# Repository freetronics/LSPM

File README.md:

Freetronics LibreSat Prototyping Module
=======================================
Copyright 2012 Freetronics Pty Ltd   www.freetronics.com  

A minimalist general-purpose prototyping module for CubeSat satellites.
Originally designed for ArduSat (www.ardusat.org) but also useful
for other satellite projects and non-space applications.

More information is available at:

  http://www.freetronics.com/lspm

The "docs" folder within this repository includes a handy copy of the
schematic in PDF format and image(s) of the pcb.

INSTALLATION
------------
The design is saved as an EAGLE project. EAGLE PCB design software is
available from www.cadsoftusa.com free for non-commercial use. To use
this project download it and place the directory containing these files
into the "eagle" directory on your computer. Then open EAGLE and
navigate to the project.

DISTRIBUTION
------------
The specific terms of distribution of this project are governed by the
license referenced below.

LICENSE
-------
Licensed under the TAPR Open Hardware License (www.tapr.org/OHL).
The "license" folder within this repository also contains a copy of
this license in plain text format.

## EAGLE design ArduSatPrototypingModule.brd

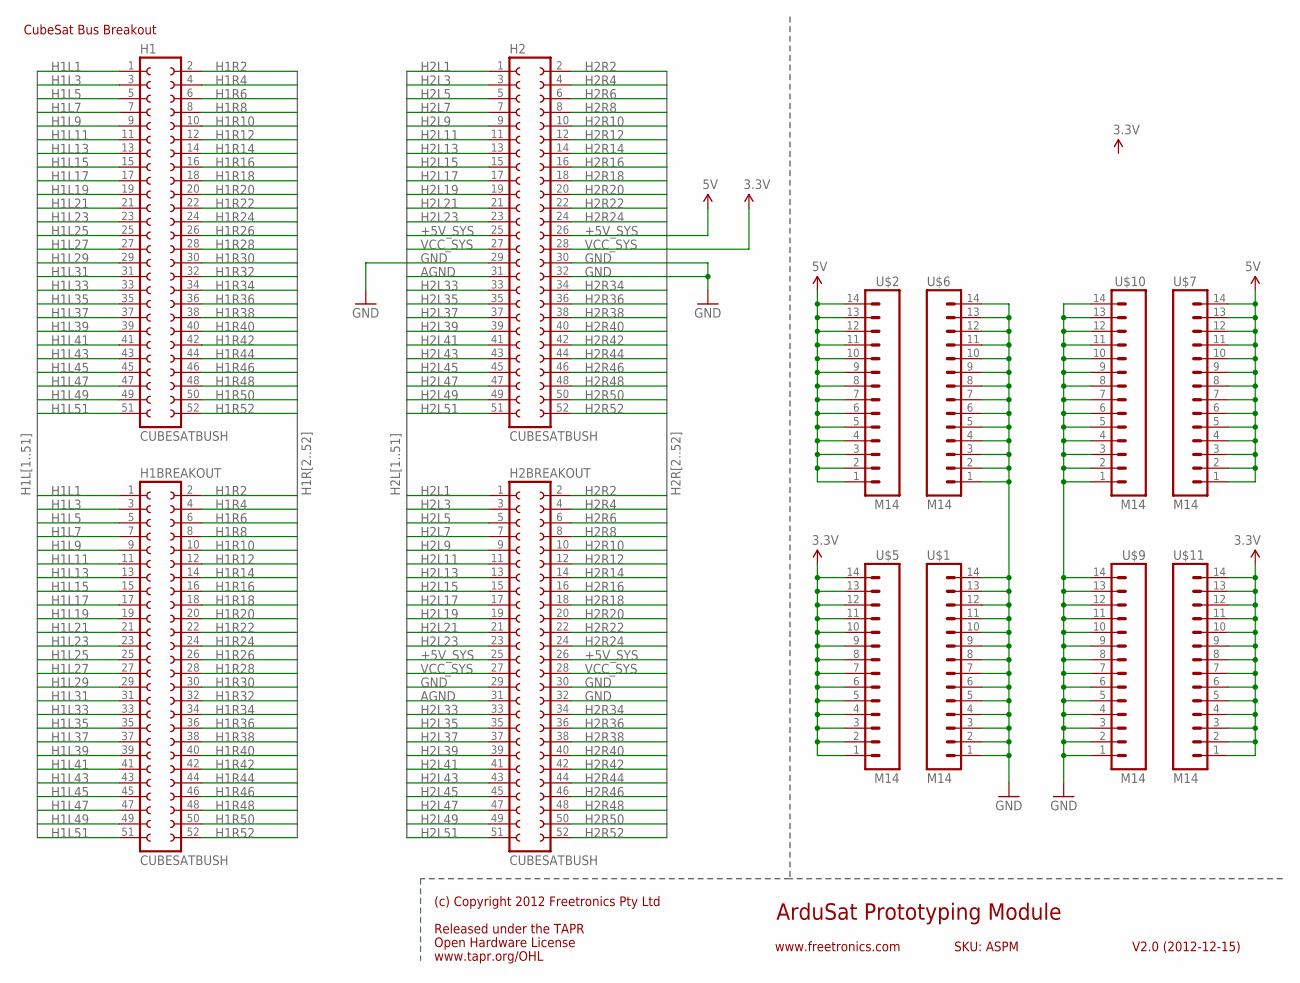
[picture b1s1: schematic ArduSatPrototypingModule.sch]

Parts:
H1, H1BREAKOUT, H2, H2BREAKOUT: CUBESATBUSH; CUBESATBUS
U$1, U$2, U$5, U$6, U$7, U$9, U$10, U$11: M14; 1X14

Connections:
+5V_SYS: H2.25, H2.26, H2BREAKOUT.25, H2BREAKOUT.26, U$2.1, U$2.2, U$2.3, U$2.4, U$2.5, U$2.6, U$2.7, U$2.8, U$2.9, U$2.10, U$2.11, U$2.12, U$2.13, U$2.14, U$7.1, U$7.2, U$7.3, U$7.4, U$7.5, U$7.6, U$7.7, U$7.8, U$7.9, U$7.10, U$7.11, U$7.12, U$7.13, U$7.14
AGND: H2.31, H2BREAKOUT.31
GND: H2.29, H2.30, H2.32, H2BREAKOUT.29, H2BREAKOUT.30, H2BREAKOUT.32, U$1.1, U$1.2, U$1.3, U$1.4, U$1.5, U$1.6, U$1.7, U$1.8, U$1.9, U$1.10, U$1.11, U$1.12, U$1.13, U$1.14, U$6.1, U$6.2, U$6.3, U$6.4, U$6.5, U$6.6, U$6.7, U$6.8, U$6.9, U$6.10, U$6.11, U$6.12, U$6.13, U$6.14, U$9.1, U$9.2, U$9.3, U$9.4, U$9.5, U$9.6, U$9.7, U$9.8, U$9.9, U$9.10, U$9.11, U$9.12, U$9.13, U$9.14, U$10.1, U$10.2, U$10.3, U$10.4, U$10.5, U$10.6, U$10.7, U$10.8, U$10.9, U$10.10, U$10.11, U$10.12, U$10.13, U$10.14
H1L1: H1.1, H1BREAKOUT.1
H1L3: H1.3, H1BREAKOUT.3
H1L5: H1.5, H1BREAKOUT.5
H1L7: H1.7, H1BREAKOUT.7
H1L9: H1.9, H1BREAKOUT.9
H1L11: H1.11, H1BREAKOUT.11
H1L13: H1.13, H1BREAKOUT.13
H1L15: H1.15, H1BREAKOUT.15
H1L17: H1.17, H1BREAKOUT.17
H1L19: H1.19, H1BREAKOUT.19
H1L21: H1.21, H1BREAKOUT.21
H1L23: H1.23, H1BREAKOUT.23
H1L25: H1.25, H1BREAKOUT.25
H1L27: H1.27, H1BREAKOUT.27
H1L29: H1.29, H1BREAKOUT.29
H1L31: H1.31, H1BREAKOUT.31
H1L33: H1.33, H1BREAKOUT.33
H1L35: H1.35, H1BREAKOUT.35
H1L37: H1.37, H1BREAKOUT.37
H1L39: H1.39, H1BREAKOUT.39
H1L41: H1.41, H1BREAKOUT.41
H1L43: H1.43, H1BREAKOUT.43
H1L45: H1.45, H1BREAKOUT.45
H1L47: H1.47, H1BREAKOUT.47
H1L49: H1.49, H1BREAKOUT.49
H1L51: H1.51, H1BREAKOUT.51
H1R2: H1.2, H1BREAKOUT.2
H1R4: H1.4, H1BREAKOUT.4
H1R6: H1.6, H1BREAKOUT.6
H1R8: H1.8, H1BREAKOUT.8
H1R10: H1.10, H1BREAKOUT.10
H1R12: H1.12, H1BREAKOUT.12
H1R14: H1.14, H1BREAKOUT.14
H1R16: H1.16, H1BREAKOUT.16
H1R18: H1.18, H1BREAKOUT.18
H1R20: H1.20, H1BREAKOUT.20
H1R22: H1.22, H1BREAKOUT.22
H1R24: H1.24, H1BREAKOUT.24
H1R26: H1.26, H1BREAKOUT.26
H1R28: H1.28, H1BREAKOUT.28
H1R30: H1.30, H1BREAKOUT.30
H1R32: H1.32, H1BREAKOUT.32
H1R34: H1.34, H1BREAKOUT.34
H1R36: H1.36, H1BREAKOUT.36
H1R38: H1.38, H1BREAKOUT.38
H1R40: H1.40, H1BREAKOUT.40
H1R42: H1.42, H1BREAKOUT.42
H1R44: H1.44, H1BREAKOUT.44
H1R46: H1.46, H1BREAKOUT.46
H1R48: H1.48, H1BREAKOUT.48
H1R50: H1.50, H1BREAKOUT.50
H1R52: H1.52, H1BREAKOUT.52
H2L1: H2.1, H2BREAKOUT.1
H2L3: H2.3, H2BREAKOUT.3
H2L5: H2.5, H2BREAKOUT.5
H2L7: H2.7, H2BREAKOUT.7
H2L9: H2.9, H2BREAKOUT.9
H2L11: H2.11, H2BREAKOUT.11
H2L13: H2.13, H2BREAKOUT.13
H2L15: H2.15, H2BREAKOUT.15
H2L17: H2.17, H2BREAKOUT.17
H2L19: H2.19, H2BREAKOUT.19
H2L21: H2.21, H2BREAKOUT.21
H2L23: H2.23, H2BREAKOUT.23
H2L33: H2.33, H2BREAKOUT.33
H2L35: H2.35, H2BREAKOUT.35
H2L37: H2.37, H2BREAKOUT.37
H2L39: H2.39, H2BREAKOUT.39
H2L41: H2.41, H2BREAKOUT.41
H2L43: H2.43, H2BREAKOUT.43
H2L45: H2.45, H2BREAKOUT.45
H2L47: H2.47, H2BREAKOUT.47
H2L49: H2.49, H2BREAKOUT.49
H2L51: H2.51, H2BREAKOUT.51
H2R2: H2.2, H2BREAKOUT.2
H2R4: H2.4, H2BREAKOUT.4
H2R6: H2.6, H2BREAKOUT.6
H2R8: H2.8, H2BREAKOUT.8
H2R10: H2.10, H2BREAKOUT.10
H2R12: H2.12, H2BREAKOUT.12
H2R14: H2.14, H2BREAKOUT.14
H2R16: H2.16, H2BREAKOUT.16
H2R18: H2.18, H2BREAKOUT.18
H2R20: H2.20, H2BREAKOUT.20
H2R22: H2.22, H2BREAKOUT.22
H2R24: H2.24, H2BREAKOUT.24
H2R34: H2.34, H2BREAKOUT.34
H2R36: H2.36, H2BREAKOUT.36
H2R38: H2.38, H2BREAKOUT.38
H2R40: H2.40, H2BREAKOUT.40
H2R42: H2.42, H2BREAKOUT.42
H2R44: H2.44, H2BREAKOUT.44
H2R46: H2.46, H2BREAKOUT.46
H2R48: H2.48, H2BREAKOUT.48
H2R50: H2.50, H2BREAKOUT.50
H2R52: H2.52, H2BREAKOUT.52
VCC_SYS: H2.27, H2.28, H2BREAKOUT.27, H2BREAKOUT.28, U$5.1, U$5.2, U$5.3, U$5.4, U$5.5, U$5.6, U$5.7, U$5.8, U$5.9, U$5.10, U$5.11, U$5.12, U$5.13, U$5.14, U$11.1, U$11.2, U$11.3, U$11.4, U$11.5, U$11.6, U$11.7, U$11.8, U$11.9, U$11.10, U$11.11, U$11.12, U$11.13, U$11.14

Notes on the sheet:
ArduSat Prototyping Module
V2.0 (2012-12-15)
www.freetronics.com
SKU: ASPM
CubeSat Bus Breakout
Released under the TAPR
Open Hardware License
www.tapr.org/OHL
(c) Copyright 2012 Freetronics Pty Ltd

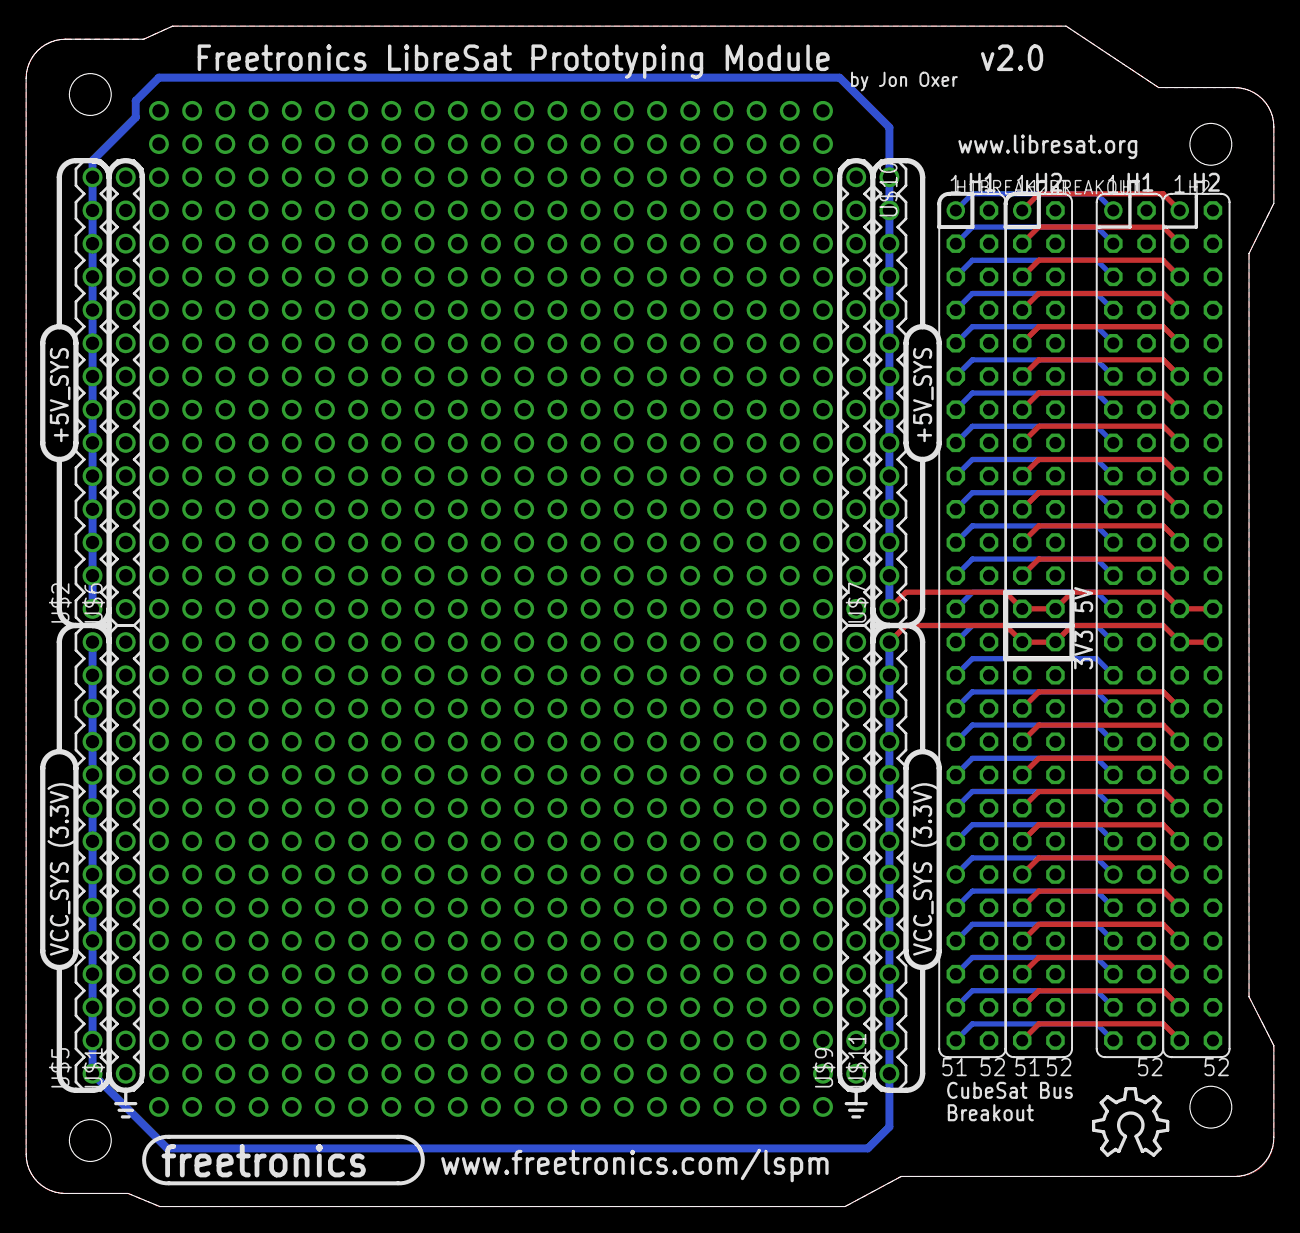
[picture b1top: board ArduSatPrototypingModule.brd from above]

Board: 4 copper layers, 95.5 x 90.3 mm, 14 parts (1 on the bottom side), 100 nets.

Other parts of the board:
U$12, U$13: OSHW_10X200_NOTEXT

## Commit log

2012-12-19 Initial project import
2012-12-19 Fixed project URL
2013-01-30 Updated README and Eagle project file
2018-03-22 Changed labels to LibreSat name
2018-03-22 Renamed files to suit LibreSat name
2018-03-22 Removed obsolete docs directory

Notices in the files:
ArduSatPrototypingModule.brd:
Copyright 2013 Freetronics Pty Ltd
parts and their libraries:
freetronics-original: Licensing: CC v3.0 Share-Alike You are welcome to use this library for commercial purposes.
